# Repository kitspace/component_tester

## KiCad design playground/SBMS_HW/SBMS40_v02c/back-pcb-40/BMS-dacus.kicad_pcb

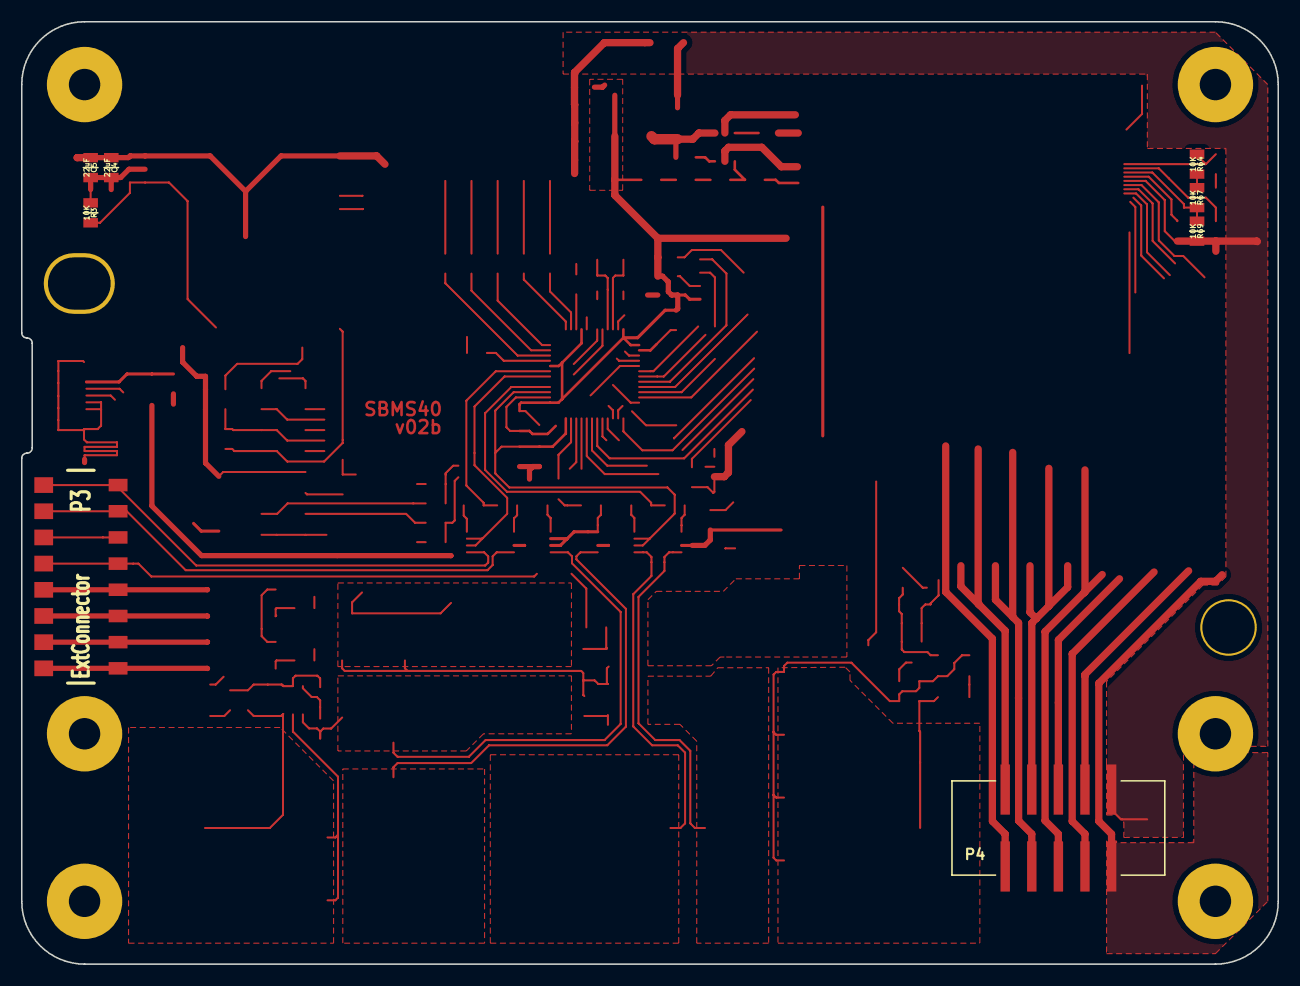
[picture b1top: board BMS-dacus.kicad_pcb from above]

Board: 2 copper layers, 120.0 x 90.0 mm, 9 parts (1 on the bottom side), 4 nets.

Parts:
C4, C5: 22uF; SM0805-dac
Logo1: VAL**; Logo1
P3: ExtConnector; SMD-8-dac1
P4: CellMon; 5x2_SMD-dac
R3, R64, R67, R69: 10K; SM0805-dac

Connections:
/VDD33: C4.2, C5.2, R3.1
/XT1: P3.4, R67.2, R69.1
GND: C4.1, C5.1, P4.1, R69.2
unnamed: R64.2, R67.1

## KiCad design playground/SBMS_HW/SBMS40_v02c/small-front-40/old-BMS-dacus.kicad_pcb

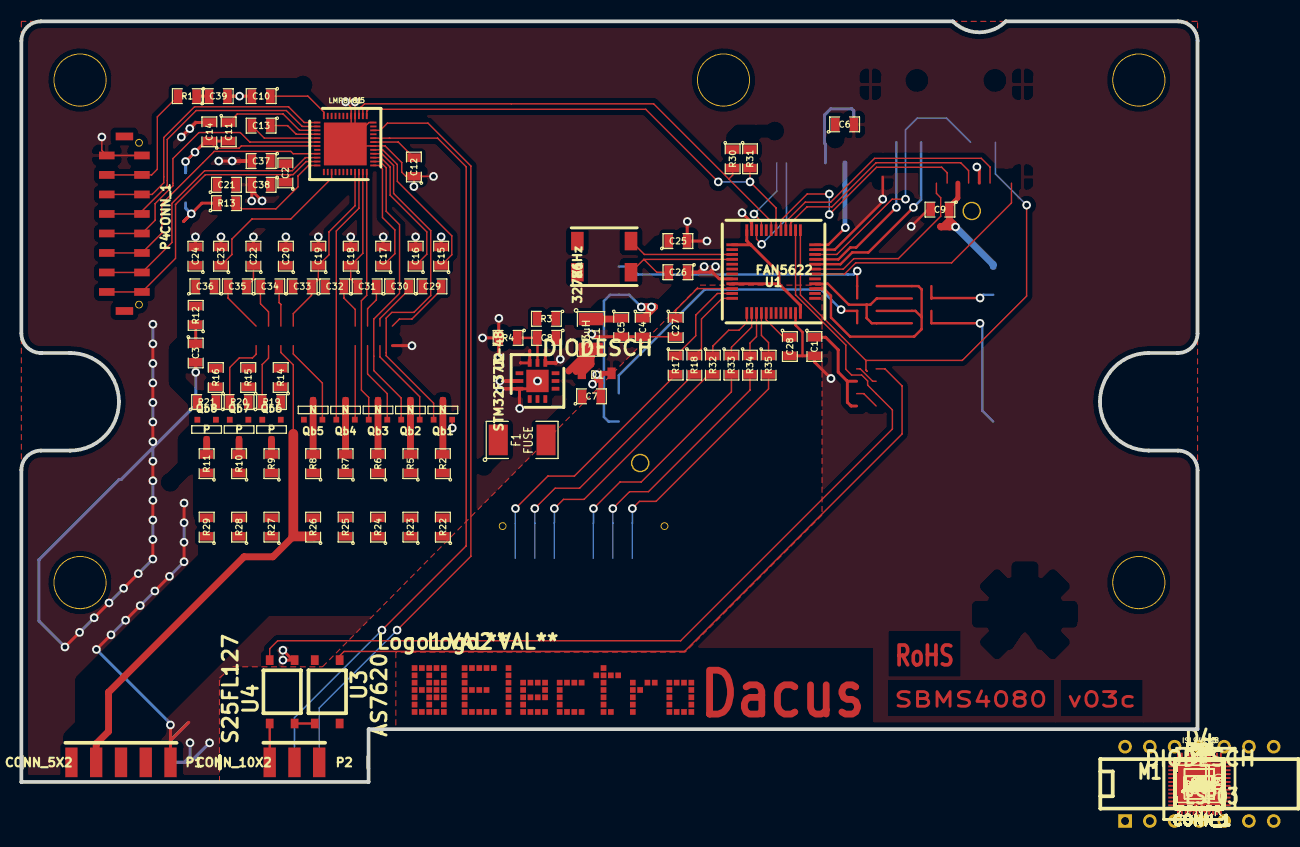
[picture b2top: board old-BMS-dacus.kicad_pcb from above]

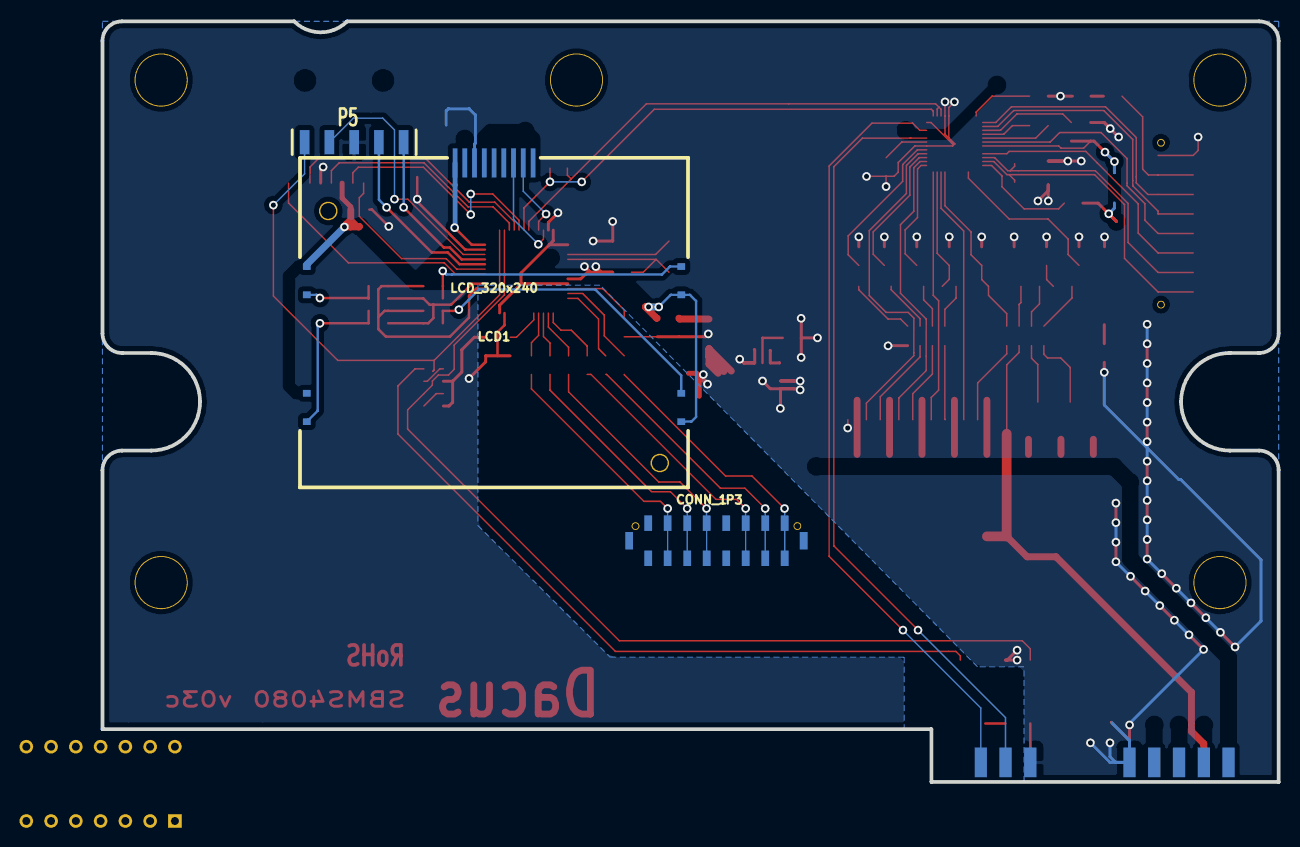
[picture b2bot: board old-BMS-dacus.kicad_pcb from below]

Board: 2 copper layers, 120.6 x 78.0 mm, 179 parts (3 on the bottom side), 123 nets.

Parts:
C1, C5, C8, C16, C17, C19, C20, C28: 22uF; SM0805
C2, C3: 22pF; SM0805
C4, C6, C9, C18, C21, C24, C27, C30, C32, C35, C37, C38, C39, C40, C41, C42, C43, C44: 100nF; SM0805
C7, C11, C12, C13, C15, C22, C23, C25, C31, C33, C36: 1uF; SM0805
C10, C14: 33nF; SM0805
C26, C29, C34: 4.7nF; SM0805
D1, D4: DIODESCH; Diode1
D2, D3, D5: BAV99U; SOT23_6
D6, D7: ZENER; DO-214AC(SMA)
F1: FUSE; SM1808
L1: 33uH; SM1210
LCD1: LCD_320x240; LCD
Logo1: VAL**; Logo1
Logo2: VAL**; Logo2
M1: ESP03; DIP-14__300
P1: CONN_5X2; 10p-con
P2: CONN_10X2; 6p-con
P3, P4: CONN_1; 60p-power
P5: CONN_1; SMD-5p-dac
P6, P7, P8, P9, P10, P11, P12, P13, P14, P15, P16, P17, P18, P19, P20, P21, P22, P23, P24: CONN_1; 1PIN_SMD
Qb1, Qb2, Qb3, Qb4, Qb5: N; SOT23-dac
Qb6, Qb7, Qb8: P; SOT23-dac
R1, R2, R3, R4, R5, R16, R17: 10k; SM0805
R6, R7, R8, R9, R10, R11, R13, R14, R25, R26, R28, R30, R32, R34, R36, R38, R40, R42, R45, R46, R52, R53: 10K; SM0805
R12, R15, R18, R19, R20, R21, R22, R29, R31, R33, R35, R37, R39, R41, R43, R44, R49: 1K; SM0805
R23, R24, R47, R48, R50, R51: 100; SM0805
R27: 1k; SM0805
R54, R55, R56, R57, R58, R59, R60, R61, R62, R63: 470K; SM0805
R64, R65, R66, R67, R68, R69, R70, R71, R72, R73, R74, R75, R76, R77, R78, R79: 12; SM0805
U1: FAN5622; LQFP48
U2: STM32F373-48; MLPQ12-1
U3: AS7620; Opto
U4: S25FL127; Opto
U5: LMP8481; QFP48-dac-2
U6, U7: LMP8481; SSOP8
U8: ISL94203; QFP48-dac-2
U9, U10: LM5050; SOT23_6
X1: 32786Hz; Quartz

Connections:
/BAT1: P1.3, Qb2.S, R29.2, R57.1, R72.1
/BAT2: P1.4, Qb3.S, R31.2, R58.1, R73.1
/BAT3: P1.5, Qb4.S, R33.2, R59.1, R74.1
/BAT4: P1.6, Qb5.S, R35.2, R60.1, R75.1
/BAT5: P1.7, R37.2, R76.1, R77.1
/BAT6: P1.8, Qb6.S, R39.2, R61.1, R78.1
/BAT7: P1.9, Qb7.S, R41.2, R62.1, R79.1
/BAT+: C4.1, C6.1, C18.1, C26.2, C31.1, D4.1, F1.1, P1.10, Qb8.S, R18.2, R43.1, R44.1, R63.1, U5.2
/BOOT0: P2.2, R8.2
/CFET: R50.1, R51.1, U8.45
/CFET1: D7.2, P15.1, R50.2, R51.2, R55.1
/CPV11: D3.1, D3.2, P19.1, U6.8
/CPV12: D3.6, P20.1, U6.1
/CPV21: D3.3, P21.1, U7.1
/CPV22: D3.4, D3.5, P22.1, U7.8
/CSI1: C34.1, C36.1, P17.1, U8.47
/CSI2: C33.1, C34.2, P16.1, U8.46
/DFET: R47.1, R48.1, U8.42
/DFET1: D6.2, P9.1, R47.2, R48.2, R54.1
/ESPFLASH: M1.7, R10.2
/ESPRST: M1.13, R14.2
/GCB1: Qb1.G, R28.2, R56.2
/GCB2: Qb2.G, R30.2, R57.2
/GCB3: Qb3.G, R32.2, R58.2
/GCB4: Qb4.G, R34.2, R59.2
/GCB5: Qb5.G, R36.2, R60.2
/GCB6: Qb6.G, R38.1, R61.2
/GCB7: Qb7.G, R40.1, R62.2
/GCB8: Qb8.G, R42.1, R63.2
/GPV1: P13.1, U9.5
/GPV2: P14.1, U10.5
/LCDLED: U1.1, U2.2
/LDMON: D6.1, P12.1, R49.2, R54.2
/LDMON1: R49.1, U8.38
/PA1: P3.1, R1.2
/PA2: P4.1, R2.2
/PA3: P5.1, R3.2
/PA4: P6.1, R4.2
/PA5: P7.1, R5.2
/PV1+: C41.2, P10.1, U9.4
/PV2+: C42.2, P11.1, U10.4
/PV+: P8.1, R23.2, R24.2, U6.2, U7.2, U9.6, U10.6
/SCFET: D7.1, P18.1, R55.2
/SCK: R16.1, U8.25
/SDA: R17.1, U8.26, U8.27
/SDADC2P: C19.2, R12.2
/SDADC14: C20.1, R15.1
/SDADC38: C28.2, R20.2
/TEMPO: R25.1, R26.1, U8.22
/USARTRX: M1.11, P2.5
/USARTTX: M1.10, P2.6
/VBATT: C40.1, R44.2, U8.48
/VC0: C21.1, R27.1, U8.17
/VC1: C24.1, R29.1, U8.15
/VC2: C27.1, R31.1, U8.13
/VC3: C30.1, R33.1, U8.11
/VC4: C32.1, R35.1, U8.9
/VC5: C35.1, R37.1, U8.7
/VC6: C39.1, R39.1, U8.5
/VC7: C43.1, R41.1, U8.3
/VC8: C44.1, R43.2, U8.1
/VDD33: C1.1, C5.1, C7.1, C8.1, C9.1, C13.1, C15.1, L1.1, LCD1.9, LCD1.10, M1.1, R9.1, R10.1, R13.1, R14.1, R19.2, U1.3, U2.1, U2.9, U3.5
/VREFSD: C16.1, C17.1, U5.6, U5.7
/XT1: P2.1, R45.2, R52.1, U8.20
/XT2: P24.1, R46.2, R53.1, U8.21
GND: C1.2, C2.2, C3.1, C4.2, C5.2, C6.2, C7.2, C8.2, C9.2, C10.2, C11.2, C12.2, C13.2, C14.2, C15.2, C16.2, C17.2, C18.2, C19.1, C20.2, C21.2, C22.1, C23.2, C24.2, C25.2, C27.2, C28.1, C30.2, C31.2, C32.2, C33.2, C35.2, C36.2, C39.2, C40.2, C43.2, C44.2, D1.1, LCD1.1, LCD1.8, M1.8, P1.1, P1.2, P2.3, P23.1, Qb1.S, R7.2, R8.1, R11.1, R21.2, R22.2, R27.2, R52.2, R53.2, R56.1, U1.2, U2.8, U3.2, U3.4, U4.4, U5.4, U6.4, U6.6, U6.7, U7.4, U7.6, U7.7, U8.0, U8.18, U8.24, U8.28, U8.29
unnamed: M1.5, R11.2
unnamed: R1.1, U2.11
unnamed: R20.1, U7.5
unnamed: D2.4, D2.5, D2.6, U5.8
unnamed: R6.1, U1.5
unnamed: LCD1.2, R9.2
unnamed: D5.2, R21.1
unnamed: D5.3, R22.1
unnamed: R6.2, R7.1
unnamed: R65.2, R73.2
unnamed: Qb2.D, R65.1
unnamed: R64.2, R72.2
unnamed: Qb1.D, R64.1
unnamed: Qb3.D, R66.1
unnamed: C22.2, U8.19
unnamed: Qb8.D, R71.1
unnamed: R18.1, U8.37
unnamed: R71.2, R79.2
unnamed: R70.2, R78.2
unnamed: Qb7.D, R70.1
unnamed: R69.2, R77.2
unnamed: Qb6.D, R69.1
unnamed: R68.2, R76.2
unnamed: Qb5.D, R68.1
unnamed: R67.2, R75.2
unnamed: Qb4.D, R67.1
unnamed: R66.2, R74.2
unnamed: R28.1, U8.16
unnamed: R30.1, U8.14
unnamed: R25.2, R45.1
unnamed: P2.4, R19.1
unnamed: R26.2, R46.1
unnamed: C29.2, U8.41
unnamed: D2.1, D2.2, D2.3, U5.1
unnamed: D4.2, U8.43
unnamed: R12.1, U5.5
unnamed: C37.1, R23.1, U9.1
unnamed: C37.2, C41.1, D5.6, U9.2, U9.3
unnamed: C38.2, C42.1, D5.4, U10.2, U10.3
unnamed: C38.1, R24.1, U10.1
unnamed: R15.2, U6.5
unnamed: C23.1, C25.1, R16.2, R17.2, U8.36
unnamed: LCD1.11, LCD1.12, LCD1.13, LCD1.14, U1.6
unnamed: C26.1, U8.39
unnamed: C2.1, U2.3, X1.1
unnamed: R38.2, U8.6
unnamed: R40.2, U8.4
unnamed: R42.2, U8.2
unnamed: R2.1, U2.12
unnamed: C11.1, C12.1, F1.2, U3.1
unnamed: C3.2, U2.4, X1.3
unnamed: C10.1, U2.10
unnamed: D1.2, L1.2
unnamed: R36.1, U8.8
unnamed: R34.1, U8.10
unnamed: R32.1, U8.12
unnamed: C29.1, U8.40

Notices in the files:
playground/SBMS_HW/SBMS40_v02c/back-pcb-40/BMS-dacus.kicad_pcb:
Electrodacus (Schematic and PCB layout released under CC-BY-SA 3.0 licence)
